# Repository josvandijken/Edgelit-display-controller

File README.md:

Controller PCB for 4 KGM M3 edgelit displays.

https://josvandijken.nl/elektronica_kgm_m3.php

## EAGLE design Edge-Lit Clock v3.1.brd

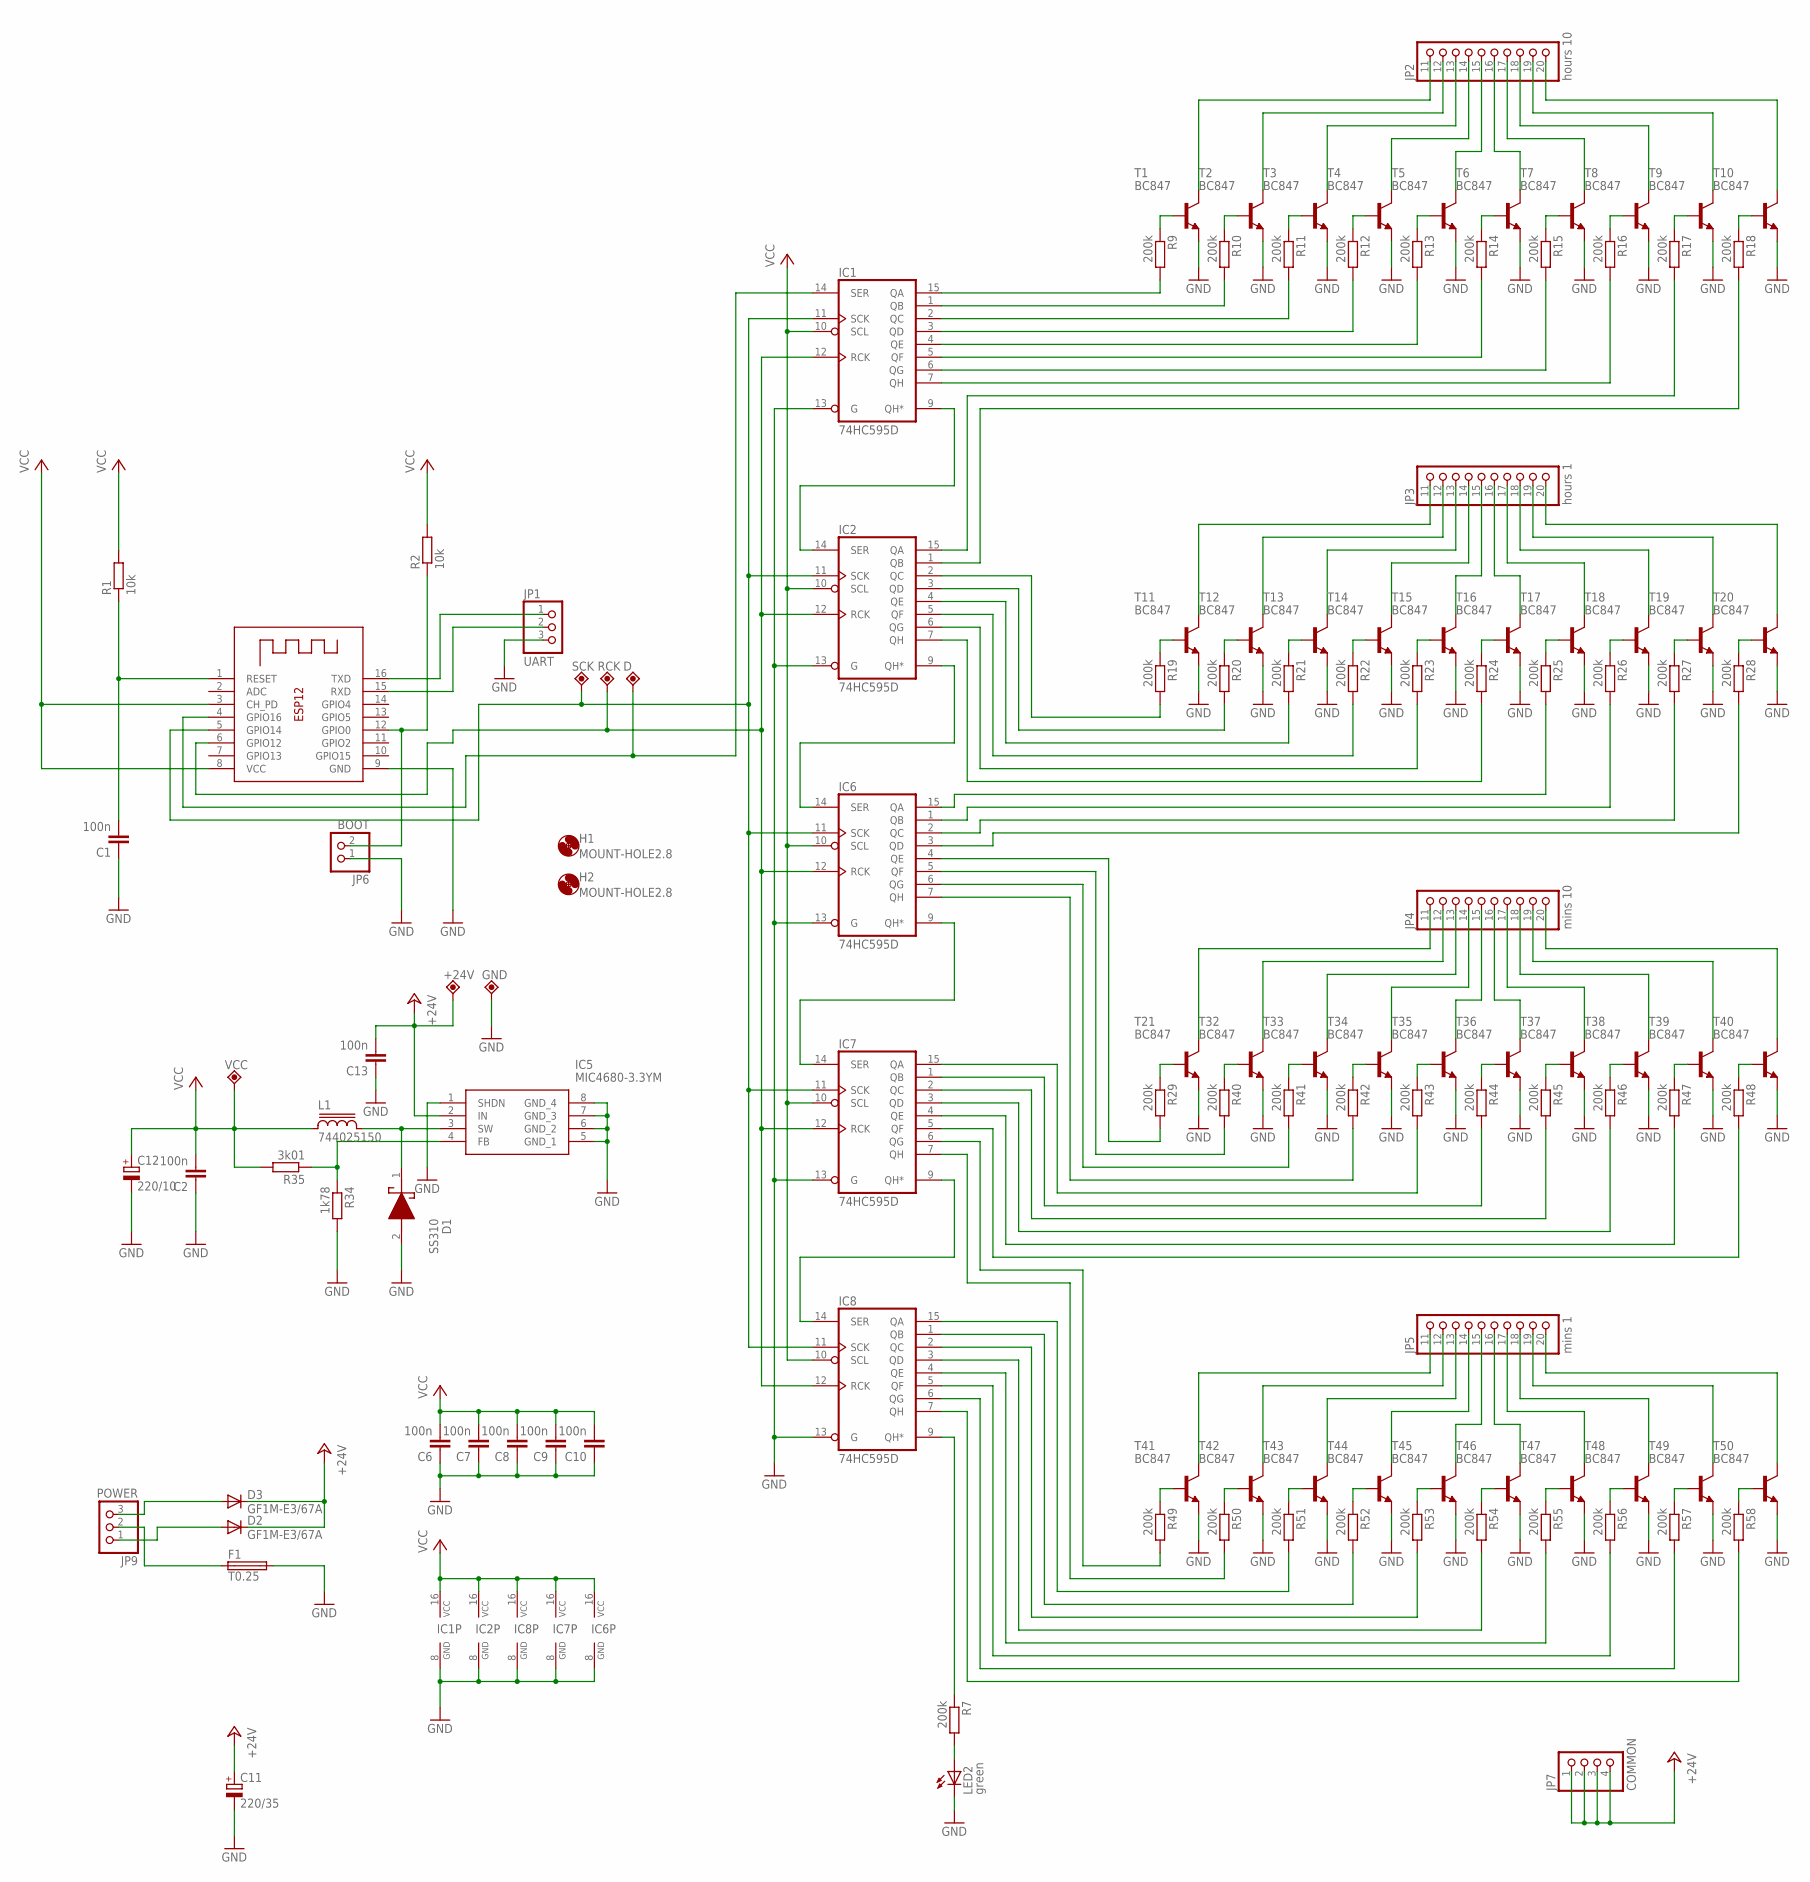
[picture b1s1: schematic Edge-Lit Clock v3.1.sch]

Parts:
+24V: TPP-PAD-024; PAD-024
C1, C2, C6, C7, C8, C9, C10, C13: 100n; C0805
C11: 220/35; SANYO-OSCON_SMD_E7
C12: 220/10; SANYO-OSCON_SMD_E7
D: TPP-PAD-024; PAD-024
D1: SS310; DIOM7959X262N
D2, D3: GF1M-E3/67A; DO214BA
F1: T0.25; TE5
GND: TPP-PAD-024; PAD-024
H1, H2: MOUNT-HOLE2.8; 2,8
IC1, IC2, IC6, IC7, IC8: 74HC595D; SO16
IC5: MIC4680-3.3YM; SOIC127P599X173-8N
JP1: UART; 1X03
JP2: hours 10; 1X10
JP3: hours 1; 1X10
JP4: mins 10; 1X10
JP5: mins 1; 1X10
JP6: BOOT; 1X02
JP7: COMMON; 1X04
JP9: POWER; 1X03
L1: 744025150
LED2: green; SML0805
R1, R2: 10k; M0805
R7, R9, R10, R11, R12, R13, R14, R15, R16, R17, R18, R19, R20, R21, R22, R23, R24, R25, R26, R27, R28, R29, R40, R41, R42, R43, R44, R45, R46, R47, R48, R49, R50, R51, R52, R53, R54, R55, R56, R57, R58: 200k; M0805
R34: 1k78; M0805
R35: 3k01; M0805
RCK: TPP-PAD-024; PAD-024
SCK: TPP-PAD-024; PAD-024
T1, T2, T3, T4, T5, T6, T7, T8, T9, T10, T11, T12, T13, T14, T15, T16, T17, T18, T19, T20, T21, T32, T33, T34, T35, T36, T37, T38, T39, T40, T41, T42, T43, T44, T45, T46, T47, T48, T49, T50: BC847; SOT23
VCC: TPP-PAD-024; PAD-024
X1: ESP12; ESP-12

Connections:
+24V: +24V.1, C11.+, C13.2, D2.C, D3.C, IC5.2 (IN), JP7.1, JP7.2, JP7.3, JP7.4
CLOCK: IC1.11 (SCK), IC2.11 (SCK), IC6.11 (SCK), IC7.11 (SCK), IC8.11 (SCK), SCK.1, X1.5 (GPIO14)
DATA: D.1, IC1.14 (SER), X1.4 (GPIO16)
GND: C1.1, C2.1, C6.1, C7.1, C8.1, C9.1, C10.1, C11.-, C12.-, C13.1, D1.2 (A), F1.2, GND.1, IC1.8 (GND), IC1.13 (G), IC2.8 (GND), IC2.13 (G), IC5.1 (SHDN), IC5.5 (GND_1), IC5.6 (GND_2), IC5.7 (GND_3), IC5.8 (GND_4), IC6.8 (GND), IC6.13 (G), IC7.8 (GND), IC7.13 (G), IC8.8 (GND), IC8.13 (G), JP1.3, JP6.1, LED2.C, R34.2, T1.2 (E), T2.2 (E), T3.2 (E), T4.2 (E), T5.2 (E), T6.2 (E), T7.2 (E), T8.2 (E), T9.2 (E), T10.2 (E), T11.2 (E), T12.2 (E), T13.2 (E), T14.2 (E), T15.2 (E), T16.2 (E), T17.2 (E), T18.2 (E), T19.2 (E), T20.2 (E), T21.2 (E), T32.2 (E), T33.2 (E), T34.2 (E), T35.2 (E), T36.2 (E), T37.2 (E), T38.2 (E), T39.2 (E), T40.2 (E), T41.2 (E), T42.2 (E), T43.2 (E), T44.2 (E), T45.2 (E), T46.2 (E), T47.2 (E), T48.2 (E), T49.2 (E), T50.2 (E), X1.9 (GND)
unnamed: R9.1, T1.1 (B)
unnamed: R10.1, T2.1 (B)
unnamed: R11.1, T3.1 (B)
unnamed: R12.1, T4.1 (B)
unnamed: R13.1, T5.1 (B)
unnamed: R14.1, T6.1 (B)
unnamed: R15.1, T7.1 (B)
unnamed: R16.1, T8.1 (B)
unnamed: R17.1, T9.1 (B)
unnamed: IC6.9 (QH*), IC7.14 (SER)
unnamed: IC1.15 (QA), R9.2
unnamed: IC1.1 (QB), R10.2
unnamed: IC1.2 (QC), R11.2
unnamed: C1.2, R1.1, X1.1 (RESET)
unnamed: IC1.3 (QD), R12.2
unnamed: JP6.2, R2.1, X1.12 (GPIO0)
unnamed: IC1.4 (QE), R13.2
unnamed: JP1.1, X1.16 (TXD)
unnamed: IC1.5 (QF), R14.2
unnamed: IC1.6 (QG), R15.2
unnamed: IC1.7 (QH), R16.2
unnamed: IC2.15 (QA), R17.2
unnamed: JP2.14 (4), T4.3 (C)
unnamed: JP1.2, X1.15 (RXD)
unnamed: IC2.9 (QH*), IC6.14 (SER)
unnamed: JP2.15 (5), T5.3 (C)
unnamed: JP2.13 (3), T3.3 (C)
unnamed: JP2.12 (2), T2.3 (C)
unnamed: JP2.11 (1), T1.3 (C)
unnamed: JP2.16 (6), T6.3 (C)
unnamed: JP2.17 (7), T7.3 (C)
unnamed: JP2.18 (8), T8.3 (C)
unnamed: JP2.19 (9), T9.3 (C)
unnamed: R18.1, T10.1 (B)
unnamed: IC2.1 (QB), R18.2
unnamed: JP2.20 (10), T10.3 (C)
unnamed: IC1.12 (RCK), IC2.12 (RCK), IC6.12 (RCK), IC7.12 (RCK), IC8.12 (RCK), RCK.1, X1.6 (GPIO12)
unnamed: D3.A, JP9.3
unnamed: R19.1, T11.1 (B)
unnamed: R20.1, T12.1 (B)
unnamed: R21.1, T13.1 (B)
unnamed: R22.1, T14.1 (B)
unnamed: R23.1, T15.1 (B)
unnamed: R24.1, T16.1 (B)
unnamed: R25.1, T17.1 (B)
unnamed: IC7.9 (QH*), IC8.14 (SER)
unnamed: R26.1, T18.1 (B)
unnamed: R27.1, T19.1 (B)
unnamed: IC2.2 (QC), R19.2
unnamed: IC2.3 (QD), R20.2
unnamed: IC2.4 (QE), R21.2
unnamed: IC2.5 (QF), R22.2
unnamed: IC2.6 (QG), R23.2
unnamed: IC2.7 (QH), R24.2
unnamed: IC6.15 (QA), R25.2
unnamed: IC6.1 (QB), R26.2
unnamed: IC6.2 (QC), R27.2
unnamed: JP3.14 (4), T14.3 (C)
unnamed: JP3.15 (5), T15.3 (C)
unnamed: JP3.13 (3), T13.3 (C)
unnamed: JP3.12 (2), T12.3 (C)
unnamed: JP3.11 (1), T11.3 (C)
unnamed: IC1.9 (QH*), IC2.14 (SER)
unnamed: JP3.16 (6), T16.3 (C)
unnamed: JP3.17 (7), T17.3 (C)
unnamed: JP3.18 (8), T18.3 (C)
unnamed: JP3.19 (9), T19.3 (C)
unnamed: R28.1, T20.1 (B)
unnamed: IC6.3 (QD), R28.2
unnamed: JP3.20 (10), T20.3 (C)
unnamed: D2.A, JP9.1
unnamed: F1.1, JP9.2
unnamed: JP4.14 (4), T34.3 (C)
unnamed: JP4.15 (5), T35.3 (C)
unnamed: JP4.13 (3), T33.3 (C)
unnamed: R29.1, T21.1 (B)
unnamed: R40.1, T32.1 (B)
unnamed: R41.1, T33.1 (B)
unnamed: R42.1, T34.1 (B)
unnamed: R43.1, T35.1 (B)
unnamed: R44.1, T36.1 (B)
unnamed: R45.1, T37.1 (B)
unnamed: R46.1, T38.1 (B)
unnamed: R47.1, T39.1 (B)
unnamed: IC6.4 (QE), R29.2
unnamed: IC6.5 (QF), R40.2
unnamed: IC6.6 (QG), R41.2
unnamed: IC6.7 (QH), R42.2
unnamed: IC7.15 (QA), R43.2
unnamed: IC7.1 (QB), R44.2
unnamed: IC7.2 (QC), R45.2
unnamed: IC7.3 (QD), R46.2
unnamed: LED2.A, R7.2
unnamed: IC7.4 (QE), R47.2
unnamed: JP4.12 (2), T32.3 (C)
unnamed: JP4.11 (1), T21.3 (C)
unnamed: JP4.16 (6), T36.3 (C)
unnamed: JP4.17 (7), T37.3 (C)
unnamed: JP4.18 (8), T38.3 (C)
unnamed: JP4.19 (9), T39.3 (C)
unnamed: JP4.20 (10), T40.3 (C)
unnamed: JP5.14 (4), T44.3 (C)
unnamed: JP5.15 (5), T45.3 (C)
unnamed: R48.1, T40.1 (B)
unnamed: IC7.5 (QF), R48.2
unnamed: JP5.13 (3), T43.3 (C)
unnamed: JP5.12 (2), T42.3 (C)
unnamed: JP5.11 (1), T41.3 (C)
unnamed: JP5.16 (6), T46.3 (C)
unnamed: JP5.17 (7), T47.3 (C)
unnamed: JP5.18 (8), T48.3 (C)
unnamed: JP5.19 (9), T49.3 (C)
unnamed: R49.1, T41.1 (B)
unnamed: R50.1, T42.1 (B)
unnamed: R51.1, T43.1 (B)
unnamed: R52.1, T44.1 (B)
unnamed: R53.1, T45.1 (B)
unnamed: R54.1, T46.1 (B)
unnamed: R55.1, T47.1 (B)
unnamed: R56.1, T48.1 (B)
unnamed: R57.1, T49.1 (B)
unnamed: IC7.6 (QG), R49.2
unnamed: IC7.7 (QH), R50.2
unnamed: IC8.15 (QA), R51.2
unnamed: IC8.1 (QB), R52.2
unnamed: IC8.2 (QC), R53.2
unnamed: IC8.3 (QD), R54.2
unnamed: IC8.4 (QE), R55.2
unnamed: IC8.5 (QF), R56.2
unnamed: IC8.6 (QG), R57.2
unnamed: JP5.20 (10), T50.3 (C)
unnamed: D1.1 (K), IC5.3 (SW), L1.2
unnamed: IC5.4 (FB), R34.1, R35.1
unnamed: IC8.9 (QH*), R7.1
unnamed: R58.1, T50.1 (B)
unnamed: IC8.7 (QH), R58.2
VCC: C2.2, C6.2, C7.2, C8.2, C9.2, C10.2, C12.+, IC1.10 (SCL), IC1.16 (VCC), IC2.10 (SCL), IC2.16 (VCC), IC6.10 (SCL), IC6.16 (VCC), IC7.10 (SCL), IC7.16 (VCC), IC8.10 (SCL), IC8.16 (VCC), L1.1, R1.2, R2.2, R35.2, VCC.1, X1.3 (CH_PD), X1.8 (VCC)

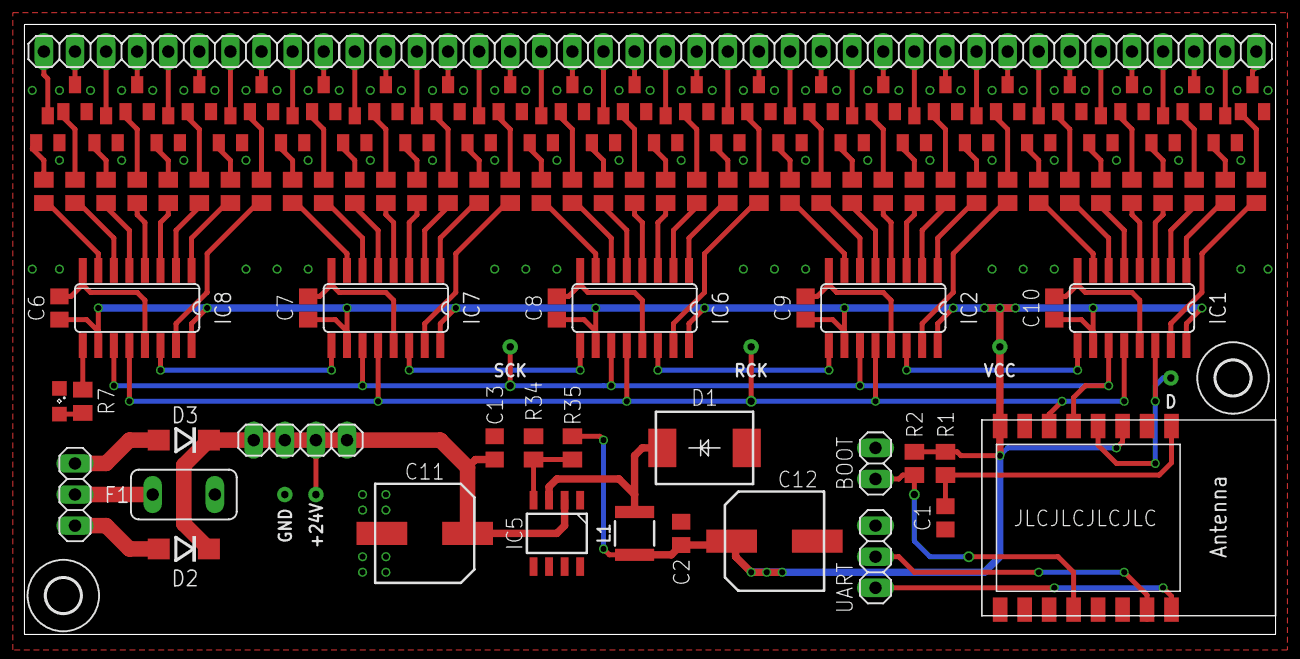
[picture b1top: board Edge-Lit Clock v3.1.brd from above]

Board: 2 copper layers, 102.2 x 49.8 mm, 124 parts (0 on the bottom side), 141 nets.

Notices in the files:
parts and their libraries:
inductor-wurth: Copyright (C) 2010, Bob Starr
testpoint: Copyright (C) 2008, Bob Starr
